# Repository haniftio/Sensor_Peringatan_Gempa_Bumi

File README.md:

# TERRADETECT

.png)
### Sistem peringatan gempa bumi menggunakan arduino uno dan sensor SW-420. Sensor ini mampu mendeteksi getaran dan gerakan halus, dengan mengintegrasikan sensor ini ke dalam sistem mikrokontroler dapat menciptakan perangkat yang dapat memberikan peringatan suara setelah gerakan terdeteksi 

Fitur utama dari sistem ini adalah kemampuannya untuk mendeteksi getaran dari gempa yang berpotensi merusak hingga membahayakan nyawa. Saat getaran terdeteksi oleh sensor SW-420, maka selanjutnya sinyal akan dikirimkan ke arduino uno dan akan mengaktifkan speaker yang berbunyi mengikuti getarannya. Switch yang ada memungkinkan penguna untuk menonaktifkan sistem jika diperlukan.

---

### Anggota
1. M. Dava Wardana - Design 3D (034)
2. M. Zakimaajid Kusuma - Program (039)
3. Zaidan Putra Daffa - Schematic & PCB (040)
4. Hanif Tio Ramadhan - Dokumentasi (042)
5. Wildanul Haq - Schematic & PCB (045)
   
---

### Komponen 
1. Arduino Uno

2. Amplifier PAM8403 3W

3. Speaker 5W

4. Sensor Getar SW-420
   
5. Switch

---

### Schematic & PCB
#### Schematic 

https://github.com/haniftio/Sensor_Peringatan_Gempa_Bumi/assets/168505785/9e40ea2a-31ad-45f1-9836-06c8c62fbed4

#### PCB

https://github.com/haniftio/Sensor_Peringatan_Gempa_Bumi/assets/168505785/ea0ed3fb-d7c9-4753-bc33-b95866b19864

##### Bottom

##### Top

##### Hasil Cetak PCB

---

### Simulasi
#### Simulasi Rangkaian By Wokwi

https://github.com/haniftio/Sensor_Peringatan_Gempa_Bumi/assets/168505785/7f55c2c7-f6d9-42f1-bedd-7ec5bf96ce46

#### Video Simulasi

[simulasi](https://youtu.be/qTaaildXK70)

Demo

https://github.com/haniftio/Sensor_Peringatan_Gempa_Bumi/assets/168505785/5472bf27-5641-4703-8057-1912f4a2773c

---

### Desain 3D
[Tutorial 3D](https://youtu.be/_sKo3YDpDic)

[Thingiverse](https://www.thingiverse.com/thing:6647639)
#### Case
##### Tampak Depan

##### Tampak Atas

##### Tampak Samping

##### Ukuran Keseluruhan

##### Untuk Visual Lebih Detail
[Box](https://github.com/haniftio/Sensor_Peringatan_Gempa_Bumi/blob/main/Desain%20Projek/Box.stl)
dan
[Tutup Box](https://github.com/haniftio/Sensor_Peringatan_Gempa_Bumi/blob/main/Desain%20Projek/Tutup.stl)

##### Hasil Cetak 3D

---

### Convert Audio

https://github.com/haniftio/Sensor_Peringatan_Gempa_Bumi/assets/168505785/96f91cc5-b915-423b-ad51-a41b3fe97962

#### Audacity
1. Buka software "Audacity".

2. Lakukan perekaman suara dengan menekan icon record (R) dan stop untuk selesai, lalu hasil suara akan muncul seperti gambar.
   
3. Blok bagian suara, kemudian menuju ke effect - Noise removal and repair - noise reduction.

4. Setelah muncul menu, kemudian pilih get noise profile - tekan ok.

   Hal ini bertujuan untuk mengurangi noise pada hasil rekaman.
5. Jika sudah dipastikan rekaman bagus, selanjutnya menuju menu file - export audio.

6. Samakan ketentuan export dengan gambar dibawah, jika selesai tekan export. Pastikan file export berformat ".RAW".

#### HXD
1. Buka software "HXD".

2. Pilih menu file - open, kemudian pilih file rekaman yang telah diekspor sebelumnya dengan format ".RAW". Selanjutnya akan muncul seperti gambar dibawah.

3. Selanjutnya pilih menu file - export - Bahasa C - dan pilih lokasi penyimpanan.

4. File dengan bahasa C itu berisi HEX dari suara rekaman yang akan dimasukkan kedalam program.

---

#### Proses Pengerjaan

https://github.com/haniftio/Sensor_Peringatan_Gempa_Bumi/assets/168505785/a3147a82-8af2-409b-9a54-c7f608828346

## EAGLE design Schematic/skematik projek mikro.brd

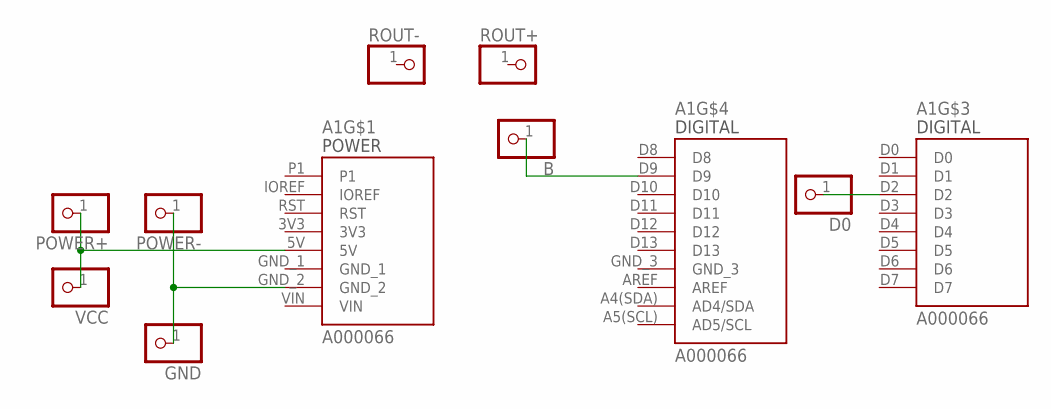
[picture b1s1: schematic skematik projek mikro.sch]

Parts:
A1: A000066; ARDUINO_A000066
B: PINHD-1X1; 1X01
D0: PINHD-1X1; 1X01
GND: PINHD-1X1; 1X01
POWER+: PINHD-1X1; 1X01
POWER-: PINHD-1X1; 1X01
ROUT+: PINHD-1X1; 1X01
ROUT-: PINHD-1X1; 1X01
VCC: PINHD-1X1; 1X01

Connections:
3V3: A1.3V3
GND_1: A1.GND_1
GND_3: A1.GND_3
unnamed: A1.5V, POWER+.1, VCC.1
unnamed: A1.GND_2, GND.1, POWER-.1
unnamed: A1.D2, D0.1
unnamed: A1.D9, B.1
VIN: A1.VIN

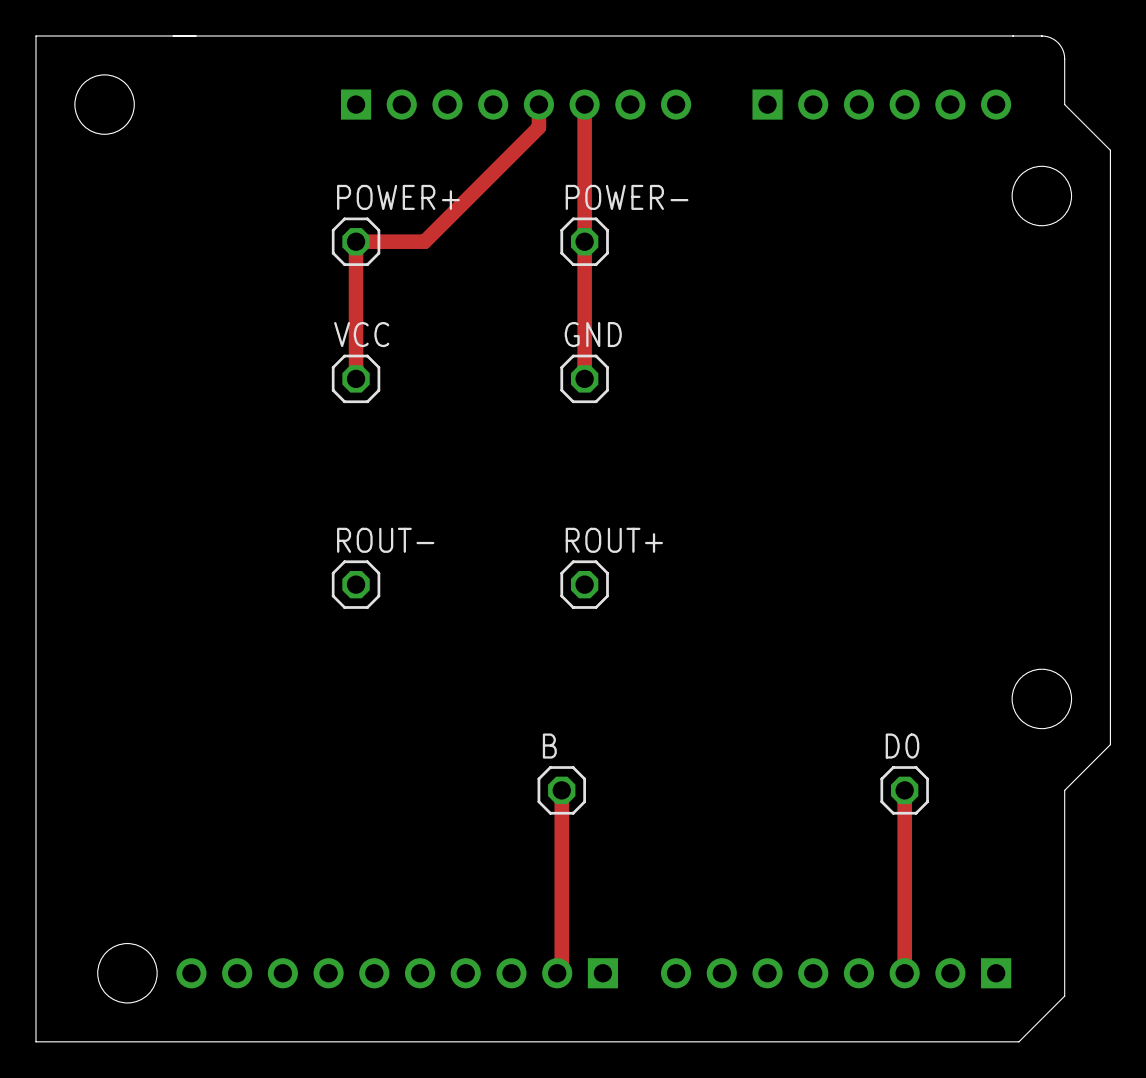
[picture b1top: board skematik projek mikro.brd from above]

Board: 2 copper layers, 59.7 x 55.9 mm, 9 parts (1 on the bottom side), 4 nets.

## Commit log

2024-05-07 README.md
2024-05-07 Create Referensi Jurnal
2024-05-07 Create referensi
2024-05-07 Create schematic
2024-05-14 Create Desain
2024-05-14 Create Referensi projek
2024-05-18 Create Revisi Desain
    untuk revisi desain dan progres revisinya
2024-05-18 Add files via upload
    Progress 20%
2024-05-18 Create Schematic Rangkaian
2024-05-18 Create Program
2024-05-18 Update Program
2024-05-19 Create Video
2024-05-19 new file
2024-05-20 Create image
2024-05-20 Update README.md\
2024-05-21 Create dokumentasi
2024-05-21 Create komponen
2024-05-21 Rename WhatsApp Image 2024-05-21 at 10.19.06.jpeg to Arduino Uno.jpeg
2024-05-21 Rename WhatsApp Image 2024-05-21 at 10.19.07.jpeg to Speaker.jpeg
2024-05-21 Rename WhatsApp Image 2024-05-21 at 10.19.09.jpeg to Spesifikasi Speaker.jpeg
2024-05-21 Rename WhatsApp Image 2024-05-21 at 10.19.10.jpeg to Modul Pam 8403 Amplifier.jpeg
2024-05-21 Rename WhatsApp Image 2024-05-21 at 10.19.17.jpeg to Sensor SW-420.jpeg
2024-05-23 Create audio
2024-05-27 Create video tutorial schematic
2024-05-27 Create Link Video Tutorial Schematic
2024-05-27 Add files via upload
    https://drive.google.com/file/d/1QlbdK9YzNm4ZqipOReZaiWnuYBX64FdY/view?usp=sharing
2024-05-27 Add files via upload
    Video Simulasi Online menggunakan WOKWI
2024-06-03 menambahkan skematik
2024-06-03 menambahkan board
2024-06-03 menambahkan video
2024-06-03 menambahkan program
